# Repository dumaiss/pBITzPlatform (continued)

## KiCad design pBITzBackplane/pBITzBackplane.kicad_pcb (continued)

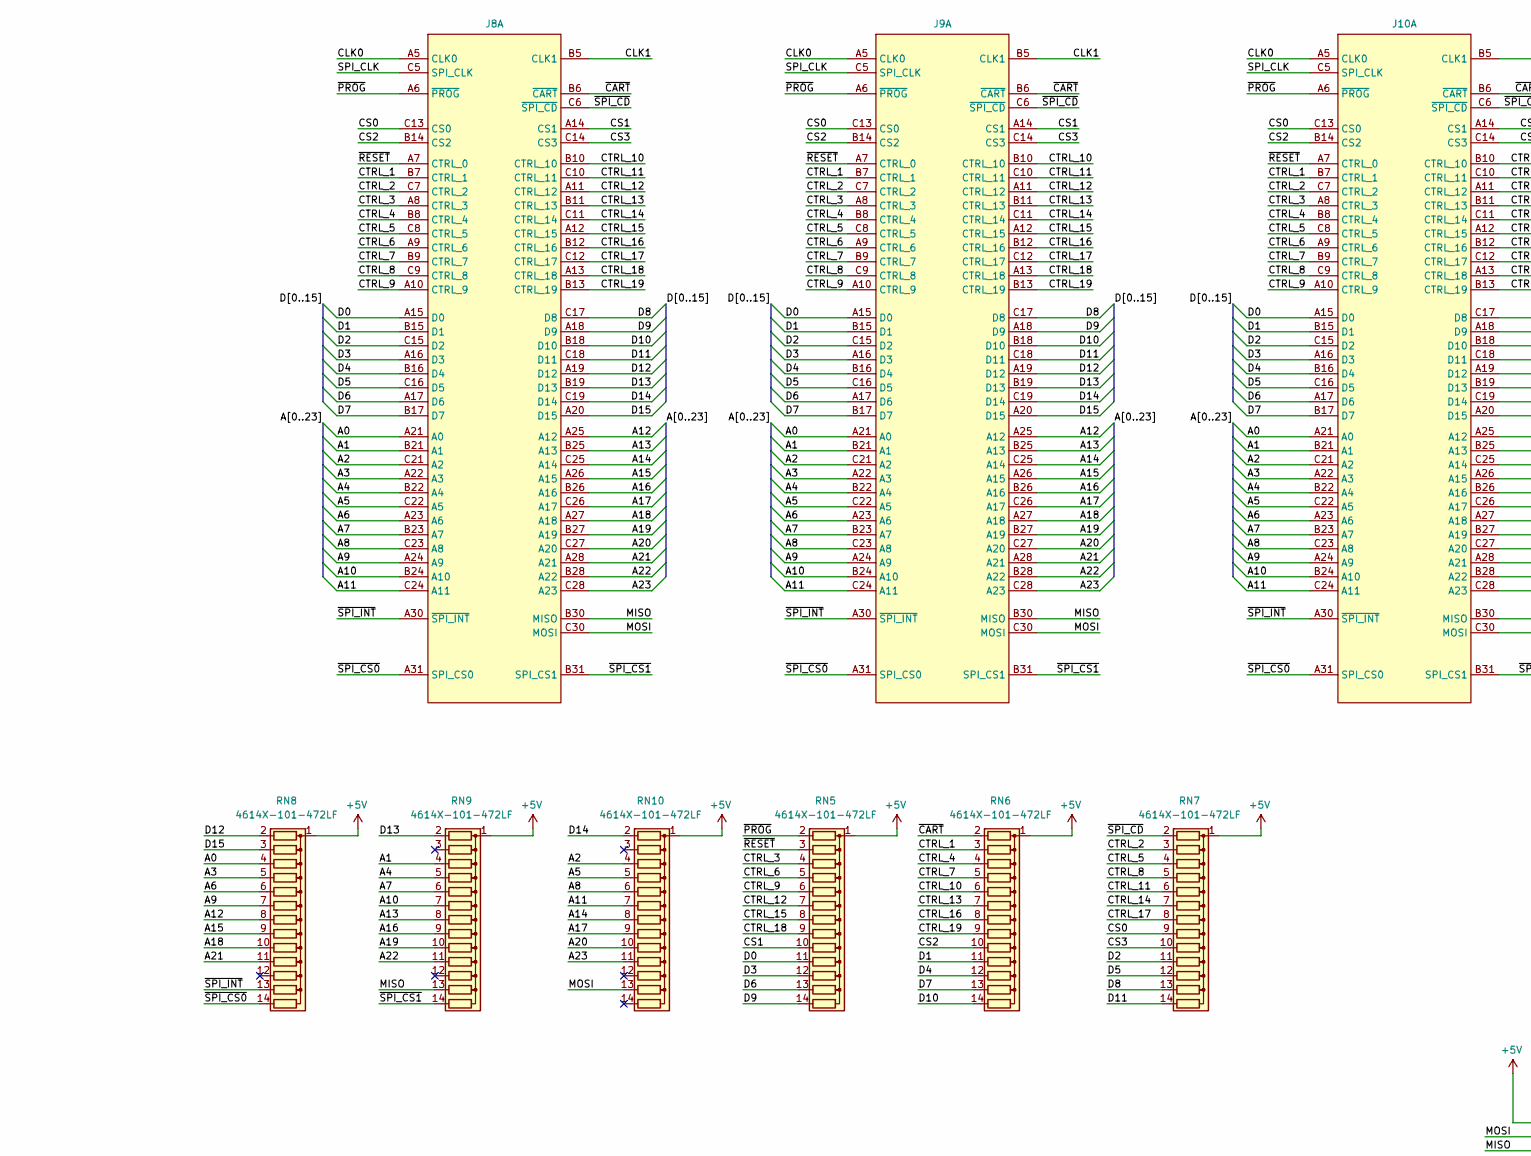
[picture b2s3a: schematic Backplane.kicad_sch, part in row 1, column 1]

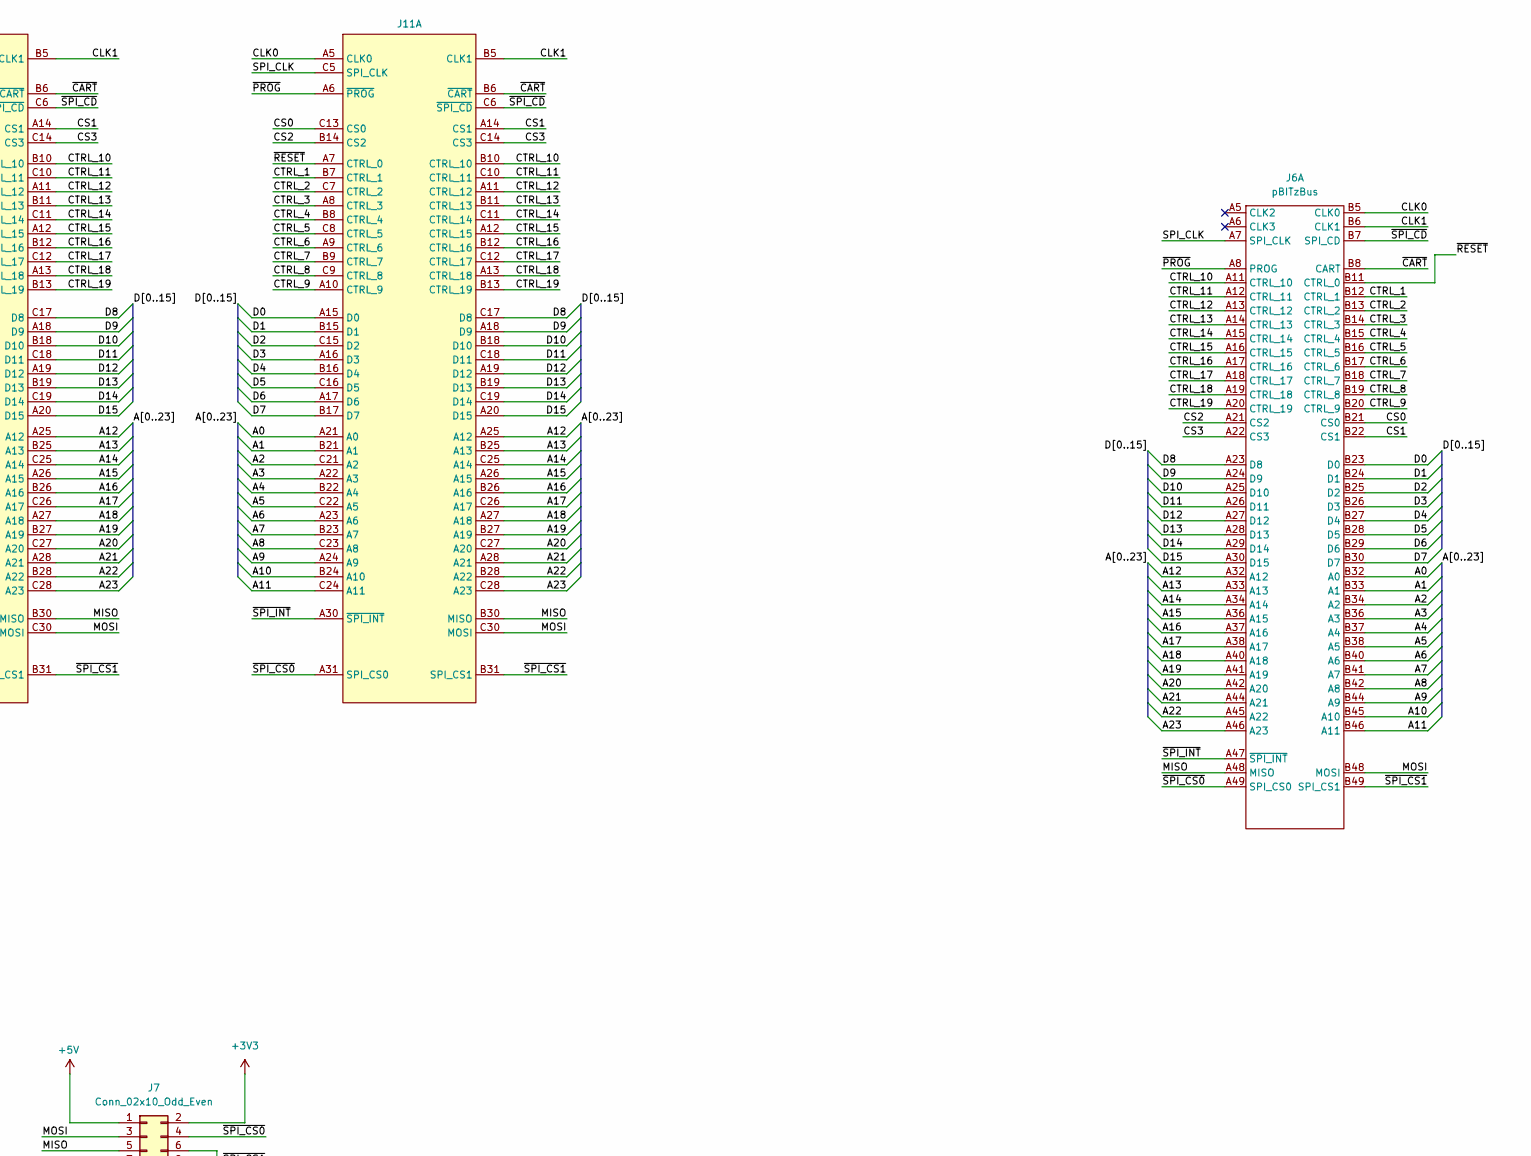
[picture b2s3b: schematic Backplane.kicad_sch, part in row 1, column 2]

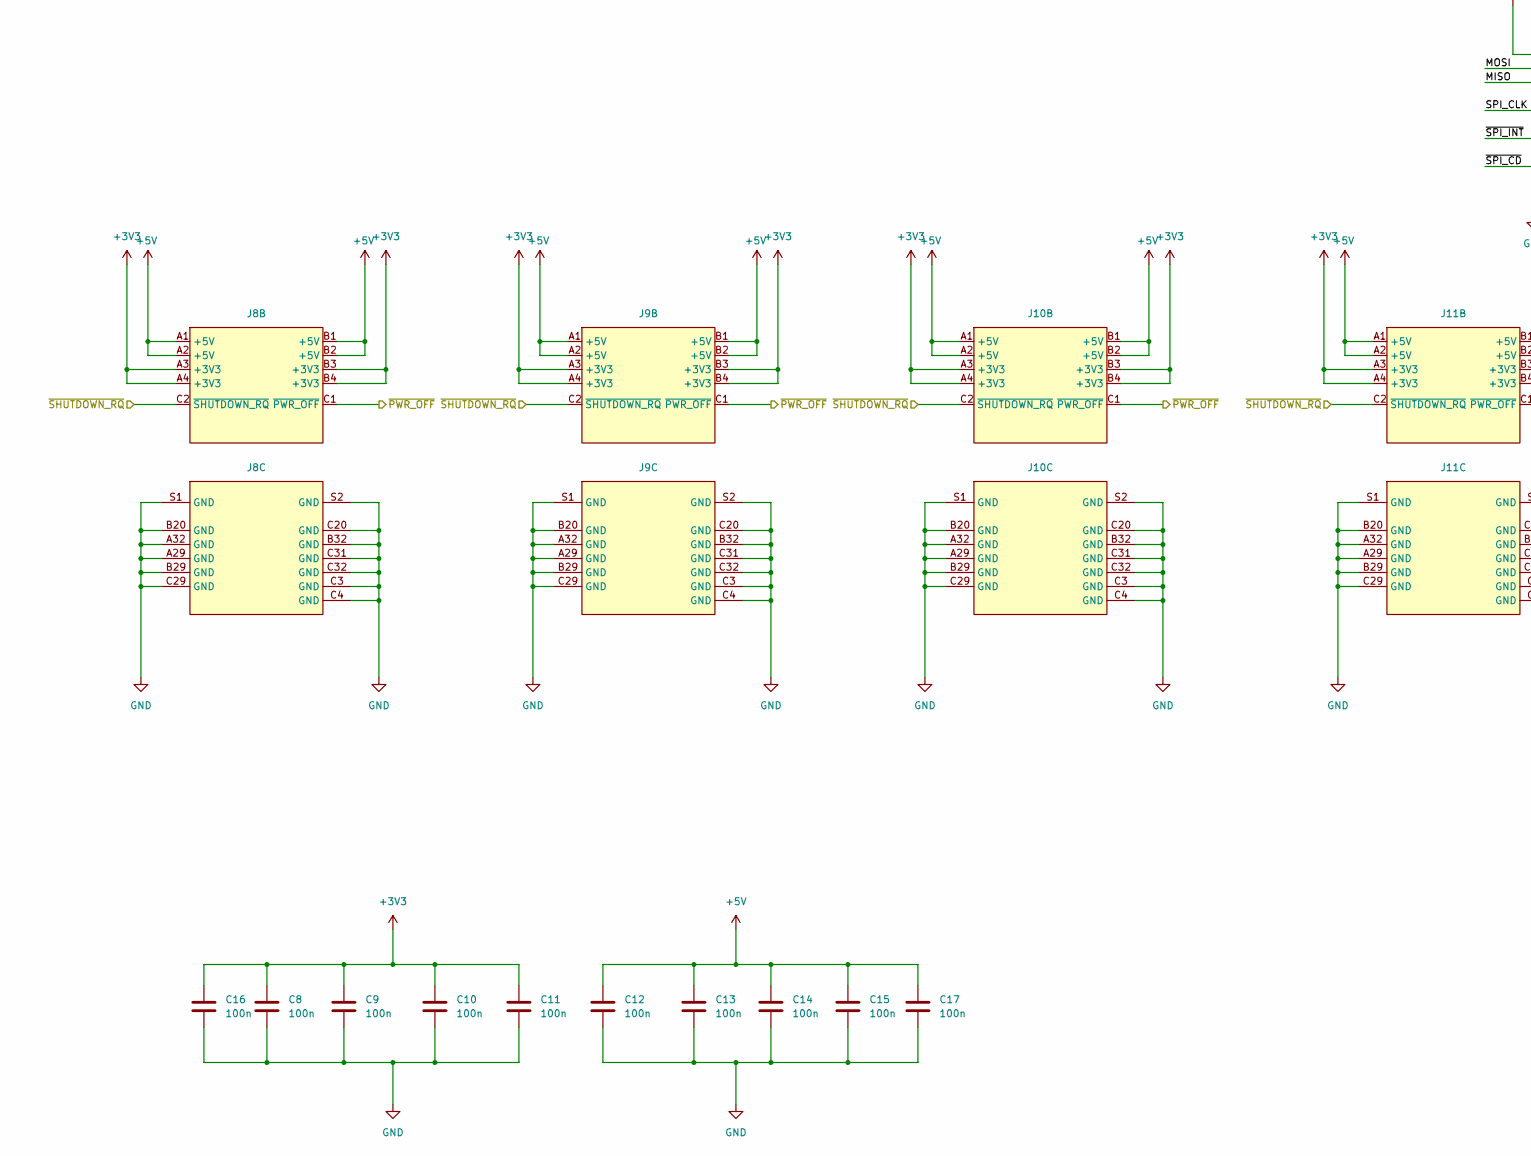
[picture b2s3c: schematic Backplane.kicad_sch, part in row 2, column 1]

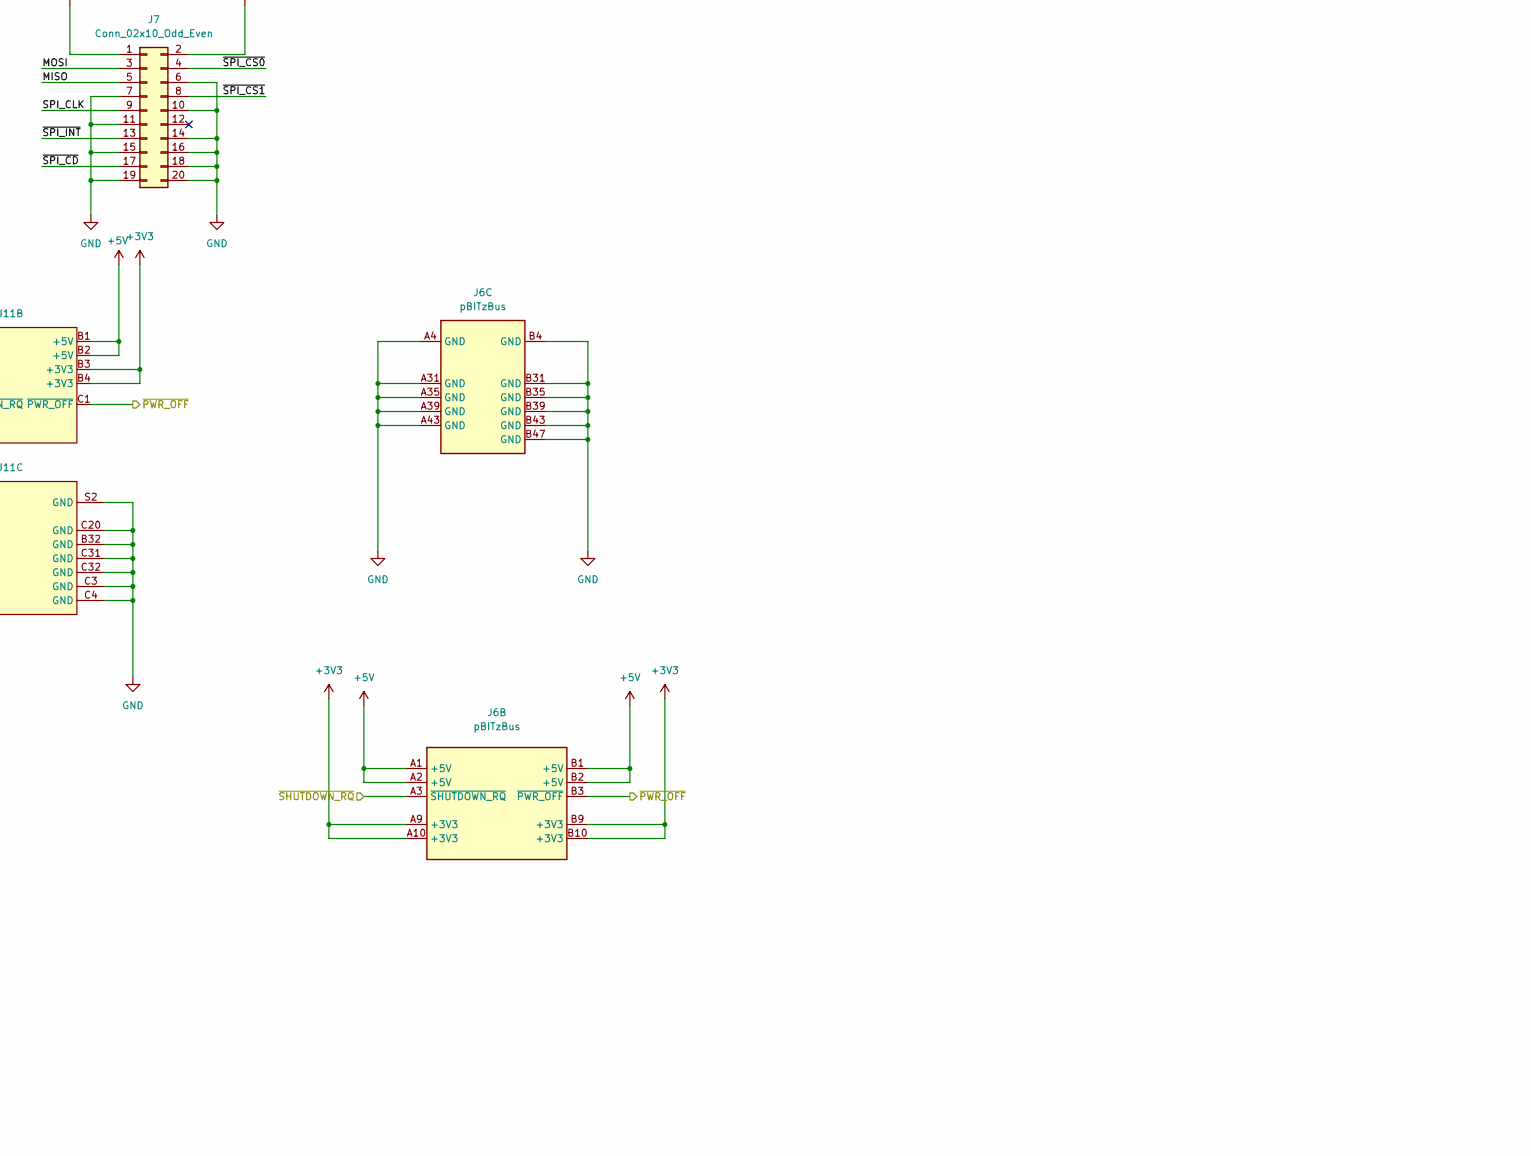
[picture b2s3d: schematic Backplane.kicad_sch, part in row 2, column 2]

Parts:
C8, C9, C10, C11, C12, C13, C14, C15, C16, C17: 100n; C_1206_3216Metric_Pad1.33x1.80mm_HandSolder; MANUFACTURER_PART_NUMBER C1206C104K3RACTU
J6: pBITzBus; SAMTEC_PCIE-098-02-X-D-RA; MANUFACTURER_PART_NUMBER PCIE-098-02-X-D-RA
J7: Conn_02x10_Odd_Even; IDC-Header_2x10_P2.54mm_Vertical; MANUFACTURER_PART_NUMBER SBH11-PBPC-D10-ST-BK
J8, J9, J10, J11: AMPHENOL_86093968114T55F1LF; MANUFACTURER_PART_NUMBER 86093968114T55F1LF
RN5, RN6, RN7, RN8, RN9, RN10: 4614X-101-472LF; R_Array_SIP14; MANUFACTURER_PART_NUMBER 4614X-101-472LF

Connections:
+3V3: C8.1, C9.1, C10.1, C11.1, C16.1, J6.A9 (+3V3), J6.A10 (+3V3), J6.B9 (+3V3), J6.B10 (+3V3), J7.2, J8.A3 (+3V3), J8.A4 (+3V3), J8.B3 (+3V3), J8.B4 (+3V3), J9.A3 (+3V3), J9.A4 (+3V3), J9.B3 (+3V3), J9.B4 (+3V3), J10.A3 (+3V3), J10.A4 (+3V3), J10.B3 (+3V3), J10.B4 (+3V3), J11.A3 (+3V3), J11.A4 (+3V3), J11.B3 (+3V3), J11.B4 (+3V3); also elsewhere on the board
+5V: C12.1, C13.1, C14.1, C15.1, C17.1, J6.A1 (+5V), J6.A2 (+5V), J6.B1 (+5V), J6.B2 (+5V), J7.1, J8.A1 (+5V), J8.A2 (+5V), J8.B1 (+5V), J8.B2 (+5V), J9.A1 (+5V), J9.A2 (+5V), J9.B1 (+5V), J9.B2 (+5V), J10.A1 (+5V), J10.A2 (+5V), J10.B1 (+5V), J10.B2 (+5V), J11.A1 (+5V), J11.A2 (+5V), J11.B1 (+5V), J11.B2 (+5V), RN5.1 (common), RN6.1 (common), RN7.1 (common), RN8.1 (common), RN9.1 (common), RN10.1 (common); also elsewhere on the board
/Backplane/A0: J6.B32 (A0), J8.A21 (A0), J9.A21 (A0), J10.A21 (A0), J11.A21 (A0), RN8.4 (R3)
/Backplane/A1: J6.B33 (A1), J8.B21 (A1), J9.B21 (A1), J10.B21 (A1), J11.B21 (A1), RN9.4 (R3)
/Backplane/A2: J6.B34 (A2), J8.C21 (A2), J9.C21 (A2), J10.C21 (A2), J11.C21 (A2), RN10.4 (R3)
/Backplane/A3: J6.B36 (A3), J8.A22 (A3), J9.A22 (A3), J10.A22 (A3), J11.A22 (A3), RN8.5 (R4)
/Backplane/A4: J6.B37 (A4), J8.B22 (A4), J9.B22 (A4), J10.B22 (A4), J11.B22 (A4), RN9.5 (R4)
/Backplane/A5: J6.B38 (A5), J8.C22 (A5), J9.C22 (A5), J10.C22 (A5), J11.C22 (A5), RN10.5 (R4)
/Backplane/A6: J6.B40 (A6), J8.A23 (A6), J9.A23 (A6), J10.A23 (A6), J11.A23 (A6), RN8.6 (R5)
/Backplane/A7: J6.B41 (A7), J8.B23 (A7), J9.B23 (A7), J10.B23 (A7), J11.B23 (A7), RN9.6 (R5)
/Backplane/A8: J6.B42 (A8), J8.C23 (A8), J9.C23 (A8), J10.C23 (A8), J11.C23 (A8), RN10.6 (R5)
/Backplane/A9: J6.B44 (A9), J8.A24 (A9), J9.A24 (A9), J10.A24 (A9), J11.A24 (A9), RN8.7 (R6)
/Backplane/A10: J6.B45 (A10), J8.B24 (A10), J9.B24 (A10), J10.B24 (A10), J11.B24 (A10), RN9.7 (R6)
/Backplane/A11: J6.B46 (A11), J8.C24 (A11), J9.C24 (A11), J10.C24 (A11), J11.C24 (A11), RN10.7 (R6)
/Backplane/A12: J6.A32 (A12), J8.A25 (A12), J9.A25 (A12), J10.A25 (A12), J11.A25 (A12), RN8.8 (R7)
/Backplane/A13: J6.A33 (A13), J8.B25 (A13), J9.B25 (A13), J10.B25 (A13), J11.B25 (A13), RN9.8 (R7)
/Backplane/A14: J6.A34 (A14), J8.C25 (A14), J9.C25 (A14), J10.C25 (A14), J11.C25 (A14), RN10.8 (R7)
/Backplane/A15: J6.A36 (A15), J8.A26 (A15), J9.A26 (A15), J10.A26 (A15), J11.A26 (A15), RN8.9 (R8)
/Backplane/A16: J6.A37 (A16), J8.B26 (A16), J9.B26 (A16), J10.B26 (A16), J11.B26 (A16), RN9.9 (R8)
/Backplane/A17: J6.A38 (A17), J8.C26 (A17), J9.C26 (A17), J10.C26 (A17), J11.C26 (A17), RN10.9 (R8)
/Backplane/A18: J6.A40 (A18), J8.A27 (A18), J9.A27 (A18), J10.A27 (A18), J11.A27 (A18), RN8.10 (R9)
/Backplane/A19: J6.A41 (A19), J8.B27 (A19), J9.B27 (A19), J10.B27 (A19), J11.B27 (A19), RN9.10 (R9)
/Backplane/A20: J6.A42 (A20), J8.C27 (A20), J9.C27 (A20), J10.C27 (A20), J11.C27 (A20), RN10.10 (R9)
/Backplane/A21: J6.A44 (A21), J8.A28 (A21), J9.A28 (A21), J10.A28 (A21), J11.A28 (A21), RN8.11 (R10)
/Backplane/A22: J6.A45 (A22), J8.B28 (A22), J9.B28 (A22), J10.B28 (A22), J11.B28 (A22), RN9.11 (R10)
/Backplane/A23: J6.A46 (A23), J8.C28 (A23), J9.C28 (A23), J10.C28 (A23), J11.C28 (A23), RN10.11 (R10)
/Backplane/CLK0: J6.B5 (CLK0), J8.A5 (CLK0), J9.A5 (CLK0), J10.A5 (CLK0), J11.A5 (CLK0)
/Backplane/CLK1: J6.B6 (CLK1), J8.B5 (CLK1), J9.B5 (CLK1), J10.B5 (CLK1), J11.B5 (CLK1)
/Backplane/CS0: J6.B21 (CS0), J8.C13 (CS0), J9.C13 (CS0), J10.C13 (CS0), J11.C13 (CS0), RN7.9 (R8)
/Backplane/CS1: J6.B22 (CS1), J8.A14 (CS1), J9.A14 (CS1), J10.A14 (CS1), J11.A14 (CS1), RN5.10 (R9)
/Backplane/CS2: J6.A21 (CS2), J8.B14 (CS2), J9.B14 (CS2), J10.B14 (CS2), J11.B14 (CS2), RN6.10 (R9)
/Backplane/CS3: J6.A22 (CS3), J8.C14 (CS3), J9.C14 (CS3), J10.C14 (CS3), J11.C14 (CS3), RN7.10 (R9)
/Backplane/CTRL_1: J6.B12 (CTRL_1), J8.B7 (CTRL_1), J9.B7 (CTRL_1), J10.B7 (CTRL_1), J11.B7 (CTRL_1), RN6.3 (R2)
/Backplane/CTRL_2: J6.B13 (CTRL_2), J8.C7 (CTRL_2), J9.C7 (CTRL_2), J10.C7 (CTRL_2), J11.C7 (CTRL_2), RN7.3 (R2)
/Backplane/CTRL_3: J6.B14 (CTRL_3), J8.A8 (CTRL_3), J9.A8 (CTRL_3), J10.A8 (CTRL_3), J11.A8 (CTRL_3), RN5.4 (R3)
/Backplane/CTRL_4: J6.B15 (CTRL_4), J8.B8 (CTRL_4), J9.B8 (CTRL_4), J10.B8 (CTRL_4), J11.B8 (CTRL_4), RN6.4 (R3)
/Backplane/CTRL_5: J6.B16 (CTRL_5), J8.C8 (CTRL_5), J9.C8 (CTRL_5), J10.C8 (CTRL_5), J11.C8 (CTRL_5), RN7.4 (R3)
/Backplane/CTRL_6: J6.B17 (CTRL_6), J8.A9 (CTRL_6), J9.A9 (CTRL_6), J10.A9 (CTRL_6), J11.A9 (CTRL_6), RN5.5 (R4)
/Backplane/CTRL_7: J6.B18 (CTRL_7), J8.B9 (CTRL_7), J9.B9 (CTRL_7), J10.B9 (CTRL_7), J11.B9 (CTRL_7), RN6.5 (R4)
/Backplane/CTRL_8: J6.B19 (CTRL_8), J8.C9 (CTRL_8), J9.C9 (CTRL_8), J10.C9 (CTRL_8), J11.C9 (CTRL_8), RN7.5 (R4)
/Backplane/CTRL_9: J6.B20 (CTRL_9), J8.A10 (CTRL_9), J9.A10 (CTRL_9), J10.A10 (CTRL_9), J11.A10 (CTRL_9), RN5.6 (R5)
/Backplane/CTRL_10: J6.A11 (CTRL_10), J8.B10 (CTRL_10), J9.B10 (CTRL_10), J10.B10 (CTRL_10), J11.B10 (CTRL_10), RN6.6 (R5)
/Backplane/CTRL_11: J6.A12 (CTRL_11), J8.C10 (CTRL_11), J9.C10 (CTRL_11), J10.C10 (CTRL_11), J11.C10 (CTRL_11), RN7.6 (R5)
/Backplane/CTRL_12: J6.A13 (CTRL_12), J8.A11 (CTRL_12), J9.A11 (CTRL_12), J10.A11 (CTRL_12), J11.A11 (CTRL_12), RN5.7 (R6)
/Backplane/CTRL_13: J6.A14 (CTRL_13), J8.B11 (CTRL_13), J9.B11 (CTRL_13), J10.B11 (CTRL_13), J11.B11 (CTRL_13), RN6.7 (R6)
/Backplane/CTRL_14: J6.A15 (CTRL_14), J8.C11 (CTRL_14), J9.C11 (CTRL_14), J10.C11 (CTRL_14), J11.C11 (CTRL_14), RN7.7 (R6)
/Backplane/CTRL_15: J6.A16 (CTRL_15), J8.A12 (CTRL_15), J9.A12 (CTRL_15), J10.A12 (CTRL_15), J11.A12 (CTRL_15), RN5.8 (R7)
/Backplane/CTRL_16: J6.A17 (CTRL_16), J8.B12 (CTRL_16), J9.B12 (CTRL_16), J10.B12 (CTRL_16), J11.B12 (CTRL_16), RN6.8 (R7)
/Backplane/CTRL_17: J6.A18 (CTRL_17), J8.C12 (CTRL_17), J9.C12 (CTRL_17), J10.C12 (CTRL_17), J11.C12 (CTRL_17), RN7.8 (R7)
/Backplane/CTRL_18: J6.A19 (CTRL_18), J8.A13 (CTRL_18), J9.A13 (CTRL_18), J10.A13 (CTRL_18), J11.A13 (CTRL_18), RN5.9 (R8)
/Backplane/CTRL_19: J6.A20 (CTRL_19), J8.B13 (CTRL_19), J9.B13 (CTRL_19), J10.B13 (CTRL_19), J11.B13 (CTRL_19), RN6.9 (R8)
/Backplane/D0: J6.B23 (D0), J8.A15 (D0), J9.A15 (D0), J10.A15 (D0), J11.A15 (D0), RN5.11 (R10)
/Backplane/D1: J6.B24 (D1), J8.B15 (D1), J9.B15 (D1), J10.B15 (D1), J11.B15 (D1), RN6.11 (R10)
/Backplane/D2: J6.B25 (D2), J8.C15 (D2), J9.C15 (D2), J10.C15 (D2), J11.C15 (D2), RN7.11 (R10)
/Backplane/D3: J6.B26 (D3), J8.A16 (D3), J9.A16 (D3), J10.A16 (D3), J11.A16 (D3), RN5.12 (R11)
/Backplane/D4: J6.B27 (D4), J8.B16 (D4), J9.B16 (D4), J10.B16 (D4), J11.B16 (D4), RN6.12 (R11)
/Backplane/D5: J6.B28 (D5), J8.C16 (D5), J9.C16 (D5), J10.C16 (D5), J11.C16 (D5), RN7.12 (R11)
/Backplane/D6: J6.B29 (D6), J8.A17 (D6), J9.A17 (D6), J10.A17 (D6), J11.A17 (D6), RN5.13 (R12)
/Backplane/D7: J6.B30 (D7), J8.B17 (D7), J9.B17 (D7), J10.B17 (D7), J11.B17 (D7), RN6.13 (R12)
/Backplane/D8: J6.A23 (D8), J8.C17 (D8), J9.C17 (D8), J10.C17 (D8), J11.C17 (D8), RN7.13 (R12)
/Backplane/D9: J6.A24 (D9), J8.A18 (D9), J9.A18 (D9), J10.A18 (D9), J11.A18 (D9), RN5.14 (R13)
/Backplane/D10: J6.A25 (D10), J8.B18 (D10), J9.B18 (D10), J10.B18 (D10), J11.B18 (D10), RN6.14 (R13)
/Backplane/D11: J6.A26 (D11), J8.C18 (D11), J9.C18 (D11), J10.C18 (D11), J11.C18 (D11), RN7.14 (R13)
/Backplane/D12: J6.A27 (D12), J8.A19 (D12), J9.A19 (D12), J10.A19 (D12), J11.A19 (D12), RN8.2 (R1)
/Backplane/D13: J6.A28 (D13), J8.B19 (D13), J9.B19 (D13), J10.B19 (D13), J11.B19 (D13), RN9.2 (R1)
/Backplane/D14: J6.A29 (D14), J8.C19 (D14), J9.C19 (D14), J10.C19 (D14), J11.C19 (D14), RN10.2 (R1)
/Backplane/D15: J6.A30 (D15), J8.A20 (D15), J9.A20 (D15), J10.A20 (D15), J11.A20 (D15), RN8.3 (R2)
/Backplane/MISO: J6.A48 (MISO), J7.5, J8.B30 (MISO), J9.B30 (MISO), J10.B30 (MISO), J11.B30 (MISO), RN9.13 (R12)
/Backplane/MOSI: J6.B48 (MOSI), J7.3, J8.C30 (MOSI), J9.C30 (MOSI), J10.C30 (MOSI), J11.C30 (MOSI), RN10.13 (R12)
/Backplane/SPI_CLK: J6.A7 (SPI_CLK), J7.9, J8.C5 (SPI_CLK), J9.C5 (SPI_CLK), J10.C5 (SPI_CLK), J11.C5 (SPI_CLK)
/Backplane/~CART: J6.B8 (CART), J8.B6 (~CART), J9.B6 (~CART), J10.B6 (~CART), J11.B6 (~CART), RN6.2 (R1)
/Backplane/~PROG: J6.A8 (PROG), J8.A6 (~PROG), J9.A6 (~PROG), J10.A6 (~PROG), J11.A6 (~PROG), RN5.2 (R1)
/Backplane/~PWR_OFF: J6.B3 (~PWR_OFF), J8.C1 (~PWR_OFF), J9.C1 (~PWR_OFF), J10.C1 (~PWR_OFF), J11.C1 (~PWR_OFF); also elsewhere on the board
/Backplane/~RESET: J6.B11 (CTRL_0), J8.A7 (CTRL_0), J9.A7 (CTRL_0), J10.A7 (CTRL_0), J11.A7 (CTRL_0), RN5.3 (R2)
/Backplane/~SHUTDOWN_RQ: J6.A3 (~SHUTDOWN_RQ), J8.C2 (~SHUTDOWN_RQ), J9.C2 (~SHUTDOWN_RQ), J10.C2 (~SHUTDOWN_RQ), J11.C2 (~SHUTDOWN_RQ); also elsewhere on the board
/Backplane/~SPI_CD: J6.B7 (SPI_CD), J7.17, J8.C6 (~SPI_CD), J9.C6 (~SPI_CD), J10.C6 (~SPI_CD), J11.C6 (~SPI_CD), RN7.2 (R1)
/Backplane/~SPI_CS0: J6.A49 (SPI_CS0), J7.4, J8.A31 (SPI_CS0), J9.A31 (SPI_CS0), J10.A31 (SPI_CS0), J11.A31 (SPI_CS0), RN8.14 (R13)
/Backplane/~SPI_CS1: J6.B49 (SPI_CS1), J7.8, J8.B31 (SPI_CS1), J9.B31 (SPI_CS1), J10.B31 (SPI_CS1), J11.B31 (SPI_CS1), RN9.14 (R13)
/Backplane/~SPI_INT: J6.A47 (~SPI_INT), J7.13, J8.A30 (~SPI_INT), J9.A30 (~SPI_INT), J10.A30 (~SPI_INT), J11.A30 (~SPI_INT), RN8.13 (R12)
GND: C8.2, C9.2, C10.2, C11.2, C12.2, C13.2, C14.2, C15.2, C16.2, C17.2, J6.A4 (GND), J6.A31 (GND), J6.A35 (GND), J6.A39 (GND), J6.A43 (GND), J6.B4 (GND), J6.B31 (GND), J6.B35 (GND), J6.B39 (GND), J6.B43 (GND), J6.B47 (GND), J7.6, J7.7, J7.10, J7.11, J7.14, J7.15, J7.16, J7.18, J7.19, J7.20, J8.A29 (GND), J8.A32 (GND), J8.B20 (GND), J8.B29 (GND), J8.B32 (GND), J8.C3 (GND), J8.C4 (GND), J8.C20 (GND), J8.C29 (GND), J8.C31 (GND), J8.C32 (GND), J8.S1 (GND), J8.S2 (GND), J9.A29 (GND), J9.A32 (GND), J9.B20 (GND), J9.B29 (GND), J9.B32 (GND), J9.C3 (GND), J9.C4 (GND), J9.C20 (GND), J9.C29 (GND), J9.C31 (GND), J9.C32 (GND), J9.S1 (GND), J9.S2 (GND), J10.A29 (GND), J10.A32 (GND), J10.B20 (GND), J10.B29 (GND), J10.B32 (GND), J10.C3 (GND), J10.C4 (GND), J10.C20 (GND), J10.C29 (GND), J10.C31 (GND), J10.C32 (GND), J10.S1 (GND), J10.S2 (GND), J11.A29 (GND), J11.A32 (GND), J11.B20 (GND), J11.B29 (GND), J11.B32 (GND), J11.C3 (GND), J11.C4 (GND), J11.C20 (GND), J11.C29 (GND), J11.C31 (GND), J11.C32 (GND), J11.S1 (GND), J11.S2 (GND); also elsewhere on the board

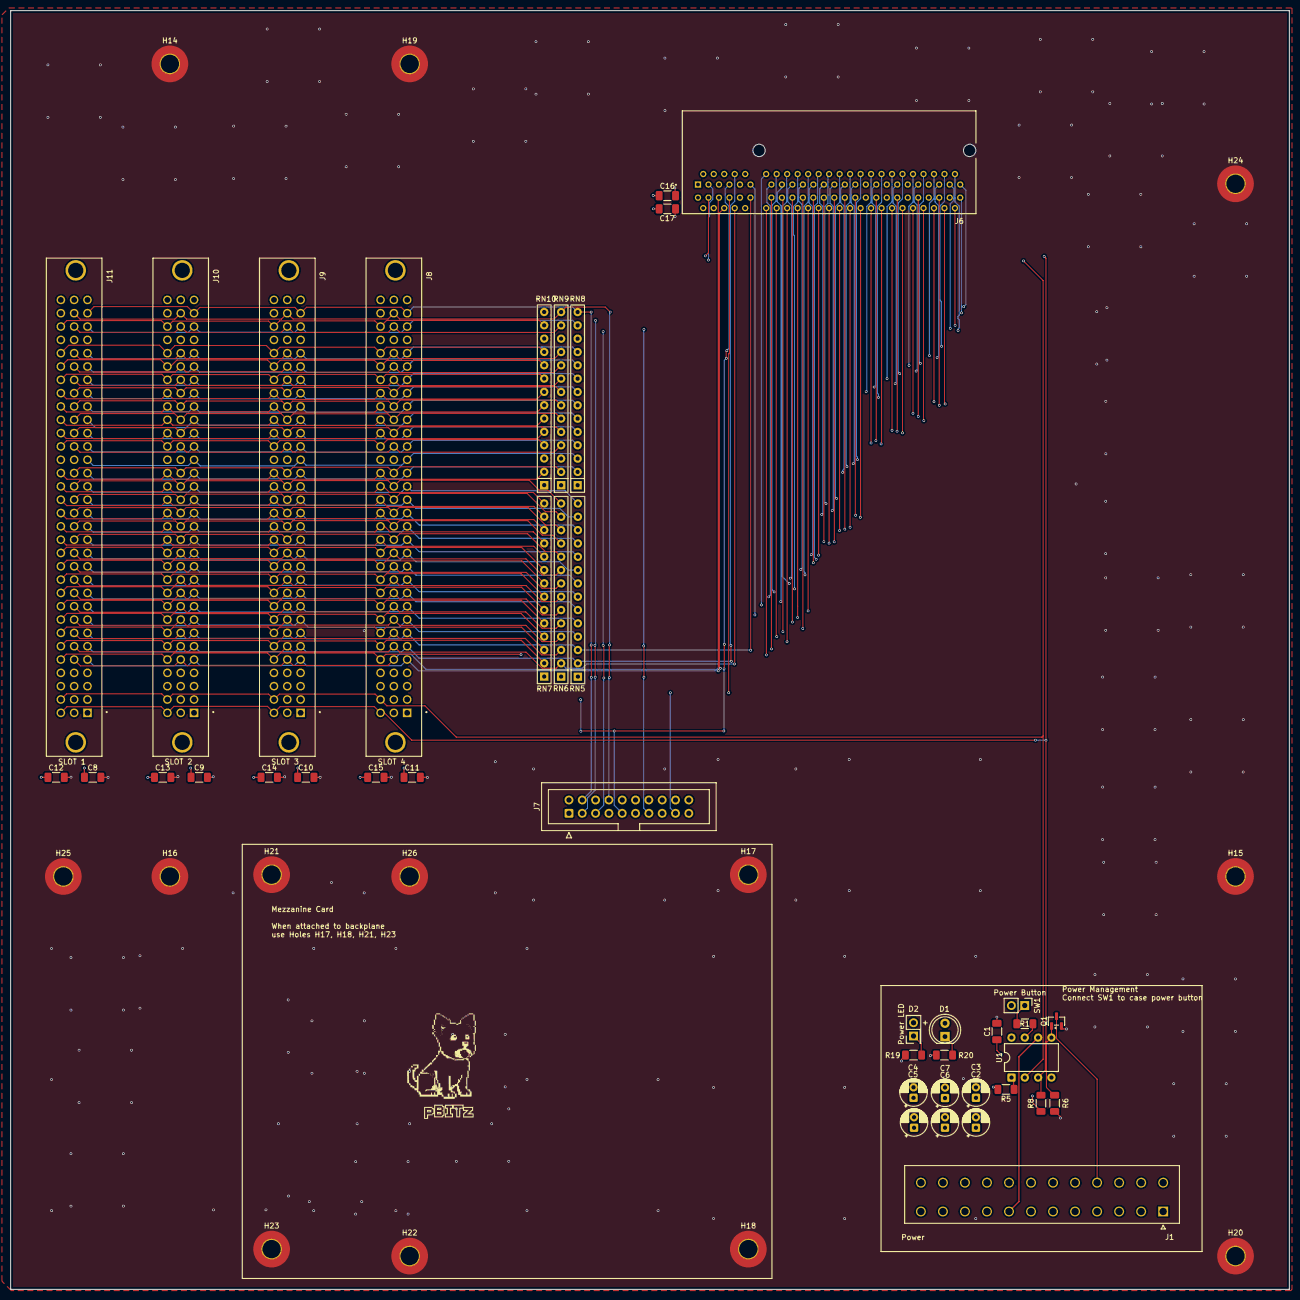
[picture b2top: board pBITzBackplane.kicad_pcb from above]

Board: 6 copper layers, 243.8 x 243.8 mm, 54 parts (0 on the bottom side), 89 nets.

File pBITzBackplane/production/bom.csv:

Designator,Footprint,Quantity,Value,LCSC Part #
"C1, C10, C11, C12, C13, C14, C15, C16, C17, C8, C9",1206,11,100n,
"C2, C4, C6",CP_Radial_D5.0mm_P2.00mm,3,100u,
"C3, C5, C7",CP_Radial_D5.0mm_P2.00mm,3,47u,
J1,MOLEX_39281243,1,ATX-24,
"J10, J11, J8, J9",AMPHENOL_86093968114T55F1LF,4,~,
J6,SAMTEC_PCIE-098-02-X-D-RA,1,pBITzBus,
J7,IDC-Header_2x10_P2.54mm_Vertical,1,Conn_02x10_Odd_Even,
Q1,SOT-23,1,BSS138,
"R1, R5, R6, R8",1206,4,10k,
"R19, R20",1206,2,4k7,
"RN10, RN5, RN6, RN7, RN8, RN9",R_Array_SIP14,6,4614X-101-472LF,
U1,DIP-8_W7.62mm,1,ATtiny85-20P,

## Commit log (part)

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2026-06-17 Add initial README for pBITzPlatform project
2026-06-17 Initial Commit... splitting the platform from the Zephyr-80 code/schem
2026-06-17 Moved modules
2026-06-17 First pass of validation
2026-06-17 don' commit lock files
2026-06-17 updated the pullups for the power on sequence pins
2026-06-17 fixed the pullups in the PCB
2026-06-17 documentation
2026-06-17 Corrections post review
2026-06-28 Added production files for mezzanine
2026-06-28 Moved all the KiCad 3D models to a new folder called "3D-Models" and renamed some of the footprints to have a more descriptive name. Added new datasheets for Analog and Peripheral components. Added n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
